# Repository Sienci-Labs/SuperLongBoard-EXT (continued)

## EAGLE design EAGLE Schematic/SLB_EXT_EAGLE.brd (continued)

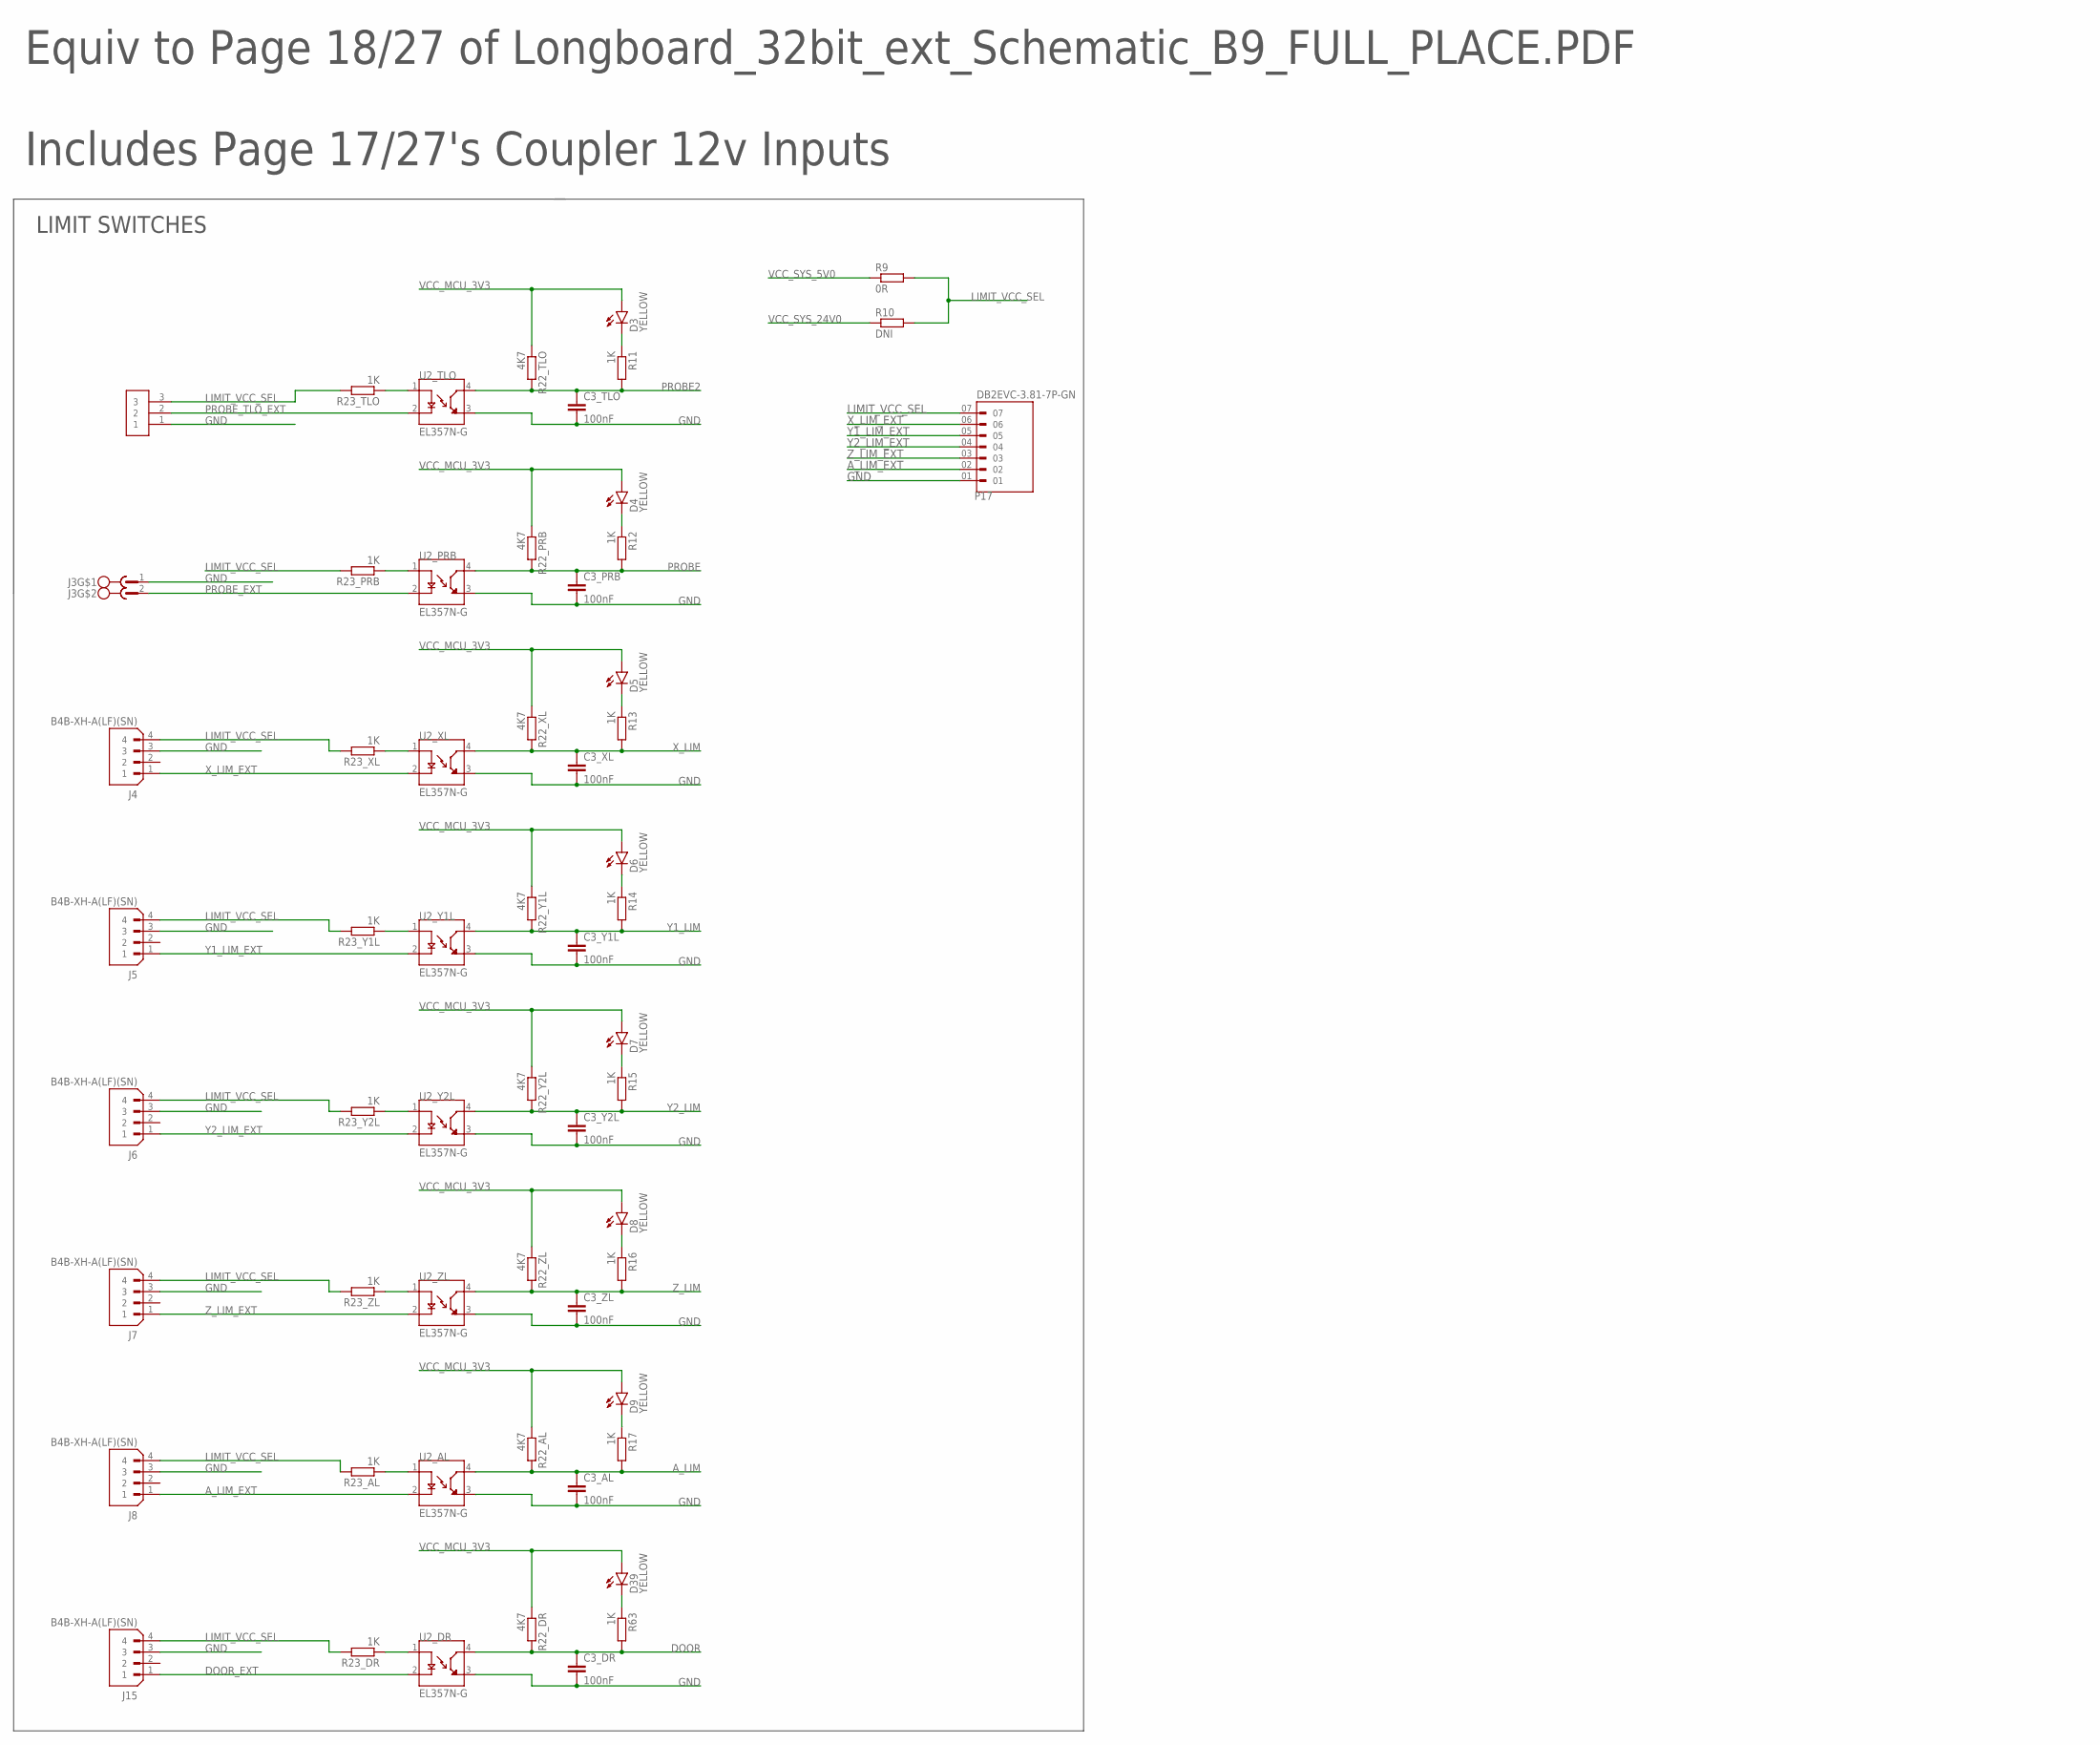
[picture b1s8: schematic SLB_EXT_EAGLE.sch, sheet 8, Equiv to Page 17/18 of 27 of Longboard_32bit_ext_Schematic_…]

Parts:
C3_AL, C3_DR, C3_PRB, C3_TLO, C3_XL, C3_Y1L, C3_Y2L, C3_ZL: 100nF; C0402
D3, D4, D5, D6, D7, D8, D9, D39: YELLOW; CHIP-LED0603
J2: Phoenix Pluggable 3.81mm 3 way; 3.81MM-3WAY-PLUGGABLE-SCREW
J3: Phoenix Pluggable 3.81mm 2 way; MC1.5/2-G-3.81
J4, J5, J6, J7, J8, J15: B4B-XH-A(LF)(SN); JST_B4B-XH-A(LF)(SN)
P17: DB2EVC-3.81-7P-GN; PHOENIX_1803471
R9: 0R; R0603
R10: DNI; R0603
R11, R12, R13, R14, R15, R16, R17, R63: 1K; R0402
R22_AL, R22_DR, R22_PRB, R22_TLO, R22_XL, R22_Y1L, R22_Y2L, R22_ZL: 4K7; R0402
R23_AL, R23_DR, R23_PRB, R23_TLO, R23_XL, R23_Y1L, R23_Y2L, R23_ZL: 1K; R0603
U2_AL, U2_DR, U2_PRB, U2_TLO, U2_XL, U2_Y1L, U2_Y2L, U2_ZL: EL357N-G; OPTO_EL357N-G

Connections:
A_LIM: C3_AL.1, R17.2, R22_AL.2, U2_AL.4 (CT); also elsewhere on the board
A_LIM_EXT: J8.1, P17.02, U2_AL.2 (C)
DOOR: C3_DR.1, R22_DR.2, R63.2, U2_DR.4 (CT); also elsewhere on the board
DOOR_EXT: J15.1, U2_DR.2 (C); also elsewhere on the board
GND: C3_AL.2, C3_DR.2, C3_PRB.2, C3_TLO.2, C3_XL.2, C3_Y1L.2, C3_Y2L.2, C3_ZL.2, J2.1, J3.1, J4.3, J5.3, J6.3, J7.3, J8.3, J15.3, P17.01, U2_AL.3 (ET), U2_DR.3 (ET), U2_PRB.3 (ET), U2_TLO.3 (ET), U2_XL.3 (ET), U2_Y1L.3 (ET), U2_Y2L.3 (ET), U2_ZL.3 (ET); also elsewhere on the board
LIMIT_VCC_SEL: J2.3, J4.4, J5.4, J6.4, J7.4, J8.4, J15.4, P17.07, R9.2, R10.2, R23_AL.2, R23_DR.2, R23_PRB.2, R23_TLO.2, R23_XL.2, R23_Y1L.2, R23_Y2L.2, R23_ZL.2
unnamed: R23_TLO.1, U2_TLO.1 (A)
unnamed: D3.C, R11.1
unnamed: R23_PRB.1, U2_PRB.1 (A)
unnamed: D4.C, R12.1
unnamed: R23_XL.1, U2_XL.1 (A)
unnamed: D5.C, R13.1
unnamed: R23_Y1L.1, U2_Y1L.1 (A)
unnamed: D6.C, R14.1
unnamed: R23_Y2L.1, U2_Y2L.1 (A)
unnamed: D7.C, R15.1
unnamed: R23_ZL.1, U2_ZL.1 (A)
unnamed: D8.C, R16.1
unnamed: R23_AL.1, U2_AL.1 (A)
unnamed: D9.C, R17.1
unnamed: R23_DR.1, U2_DR.1 (A)
unnamed: D39.C, R63.1
PROBE: C3_PRB.1, R12.2, R22_PRB.2, U2_PRB.4 (CT); also elsewhere on the board
PROBE2: C3_TLO.1, R11.2, R22_TLO.2, U2_TLO.4 (CT); also elsewhere on the board
PROBE_EXT: J3.2, U2_PRB.2 (C)
PROBE_TLO_EXT: J2.2, U2_TLO.2 (C)
VCC_MCU_3V3: D3.A, D4.A, D5.A, D6.A, D7.A, D8.A, D9.A, D39.A, R22_AL.1, R22_DR.1, R22_PRB.1, R22_TLO.1, R22_XL.1, R22_Y1L.1, R22_Y2L.1, R22_ZL.1; also elsewhere on the board
VCC_SYS_5V0: R9.1; also elsewhere on the board
VCC_SYS_24V0: R10.1; also elsewhere on the board
X_LIM: C3_XL.1, R13.2, R22_XL.2, U2_XL.4 (CT); also elsewhere on the board
X_LIM_EXT: J4.1, P17.06, U2_XL.2 (C)
Y1_LIM: C3_Y1L.1, R14.2, R22_Y1L.2, U2_Y1L.4 (CT); also elsewhere on the board
Y1_LIM_EXT: J5.1, P17.05, U2_Y1L.2 (C)
Y2_LIM: C3_Y2L.1, R15.2, R22_Y2L.2, U2_Y2L.4 (CT); also elsewhere on the board
Y2_LIM_EXT: J6.1, P17.04, U2_Y2L.2 (C)
Z_LIM: C3_ZL.1, R16.2, R22_ZL.2, U2_ZL.4 (CT); also elsewhere on the board
Z_LIM_EXT: J7.1, P17.03, U2_ZL.2 (C)

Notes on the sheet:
Equiv to Page 18/27 of Longboard_32bit_ext_Schematic_B9_FULL_PLACE.PDF Includes Page 17/27's Coupler 12v Inputs
LIMIT SWITCHES

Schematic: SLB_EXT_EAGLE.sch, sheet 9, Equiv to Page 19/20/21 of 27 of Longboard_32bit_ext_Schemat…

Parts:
C10: 100nF; C0402; LCSC_PART C576517
C11, C12, C14, C15, C58, C59: 10uF; C1206; LCSC_PART C576517
C13, C52, C53: 22uF; C0805; LCSC_PART C576517
C16: 10nF; C0402; LCSC_PART C576517
C17: 10pF; C0603; LCSC_PART C576517
C18, C19, C85: 8.2nF; C0603; LCSC_PART C576517
C54: 4.7uF; C0603
C55: 22uF; C0603; LCSC_PART C576517
C56: 100uF; CAPMP3528X210N
C57: 100uF; SANYO-OSCON_SMD_C6
C69, C76: 100nF 100v; C0805; LCSC_PART C576517
C74: 10uF 100V; C0603; LCSC_PART C576517
C75: 2.2uF; C1206; LCSC_PART C576517
C77, C78, C79, C80, C89, C90: 10uF; C1206
C81: 100nF 100v; C0603; LCSC_PART C576517
C83: 1.5nF; C0603; LCSC_PART C576517
C84: 5.6pF; C0402; LCSC_PART C576517
C86: 220pF; C0603; LCSC_PART C576517
C113: 100nF; C0603; LCSC_PART C576517
C115: 10uF 100V; C1210; LCSC_PART C576517
C144, C145: 10uF 100V; C0805; LCSC_PART C576517
D14: SS210; DO-214AC; LCSC_PART C14996
D19: SS54; DO-214AC; LCSC_PART C14996
D20, D24: GREEN; CHIP-LED0603
D23: 1SMAF4734A; SMAF-ZDIODE
D32: RED; CHIP-LED0805
J19: DNI; 1X02
L3: 22uH; YSPI0630A-220M
L5: 68uH; DR125
L7: 150mΩ ±25% 220Ω@100MHz 0805 Ferrite Beads ROHS; FB402; LCSC_PART C139188
L8, L9, L12: 150mΩ ±25% 220Ω@100MHz 0805 Ferrite Beads ROHS; FB805; LCSC_PART C139188
P10: DB2ERC-5.08-2P-GN; MSTBA2
P23: 22284020; 1X02
P24: 1803329; PHOENIX_1803329
Q3: 2N7002-7-F; SOT-23
Q14, Q15: CSD19538Q3A
R29, R134: 2R2; R0603
R30: 180K; R0603
R38, R55, R82, R83: 10K; R0603
R43: 8K2; R0603
R56: 47k; R0603
R57: 1K91; R0603
R111, R196: 1K; R0603
R125, R132: 20K; R0603
R167: 1k5; R0603
R175: 4K7; R0603
R176: 18K; R0603
R177, R184: 5K1; R0603
R178: 620R; R0603
R179: 39K; R0603
S1: SS-12D11G5R; XKBENTERPRISESS-12D11G5R
U16: TPS54331DR; SOIC127P599X175-8N
U24: LM5146QRGYTQ1; RGY0020B
U43: EL357N-G; OPTO_EL357N-G
VR1: AMS1117-3.3

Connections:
COMP: C85.1, C86.1, U24.4 (COMP)
ESTOP_5V_EN: P23.1, P24.06
FEEDBACK24V: C83.2, C86.2, R176.1, R177.1, R178.2, U24.5 (FB)
GND: C11.2, C12.2, C13.2, C14.2, C15.2, C16.2, C17.1, C18.2, C19.1, C52.2, C53.2, C54.2, C58.2, C59.2, C69.2, C74.2, C75.2, C76.2, C77.2, C78.2, C79.2, C80.2, C84.2, C89.2, C90.2, C113.2, C115.2, C144.2, C145.2, D19.2 (A), J19.2, L9.1, P10.2, P24.01, Q15.1 (SOURCE), Q15.2 (SOURCE), Q15.3 (SOURCE), R43.2, R57.2, R82.2, R83.2, R178.1, R179.2, S1.LEFT, U16.7 (GND), U24.6 (AGND), U24.9 (NC_2), U24.12 (PGND), U24.15 (EP_2), U24.16 (NC), U24.21 (EP), U43.2 (C), VR1.1 (ADJ/GND); also elsewhere on the board
HALT_EXT: D32.C, Q3.P3 (D), R38.2; also elsewhere on the board
INPUT_VCC: C89.1, C90.1, L7.1, P10.1; also elsewhere on the board
MACRO1_EXT: P24.04; also elsewhere on the board
MACRO2_EXT: P24.03; also elsewhere on the board
MCU_GND: C55.2, C56.2, C57.-, D23.A, L9.2, Q3.P2 (S); also elsewhere on the board
MOTOR_NPGD: Q3.P1 (G); also elsewhere on the board
MOTOR_VCC_80V: R184.2; also elsewhere on the board
unnamed: D14.2 (A), L7.2
unnamed: C10.2, D19.1 (C), L3.1, U16.8 (PH)
unnamed: R29.2, U24.20 (VIN)
unnamed: C76.1, U24.3 (SS_TRK)
unnamed: R125.2, U24.8 (SYNCIN)
unnamed: R132.2, U24.10 (PGOOD)
unnamed: C75.1, R125.1, R132.1, U24.14 (VCC)
unnamed: Q14.4 (GATE), U24.18 (HO)
unnamed: C85.2, R177.2
unnamed: Q15.4 (GATE), U24.13 (LO)
unnamed: C84.1, R167.1, U24.11 (ILIM)
unnamed: R134.1, U24.17 (BST)
unnamed: C81.1, R134.2
unnamed: C81.2, L5.1, Q14.1 (SOURCE), Q14.2 (SOURCE), Q14.3 (SOURCE), Q15.5 (DRAIN), Q15.6 (DRAIN), Q15.7 (DRAIN), Q15.8 (DRAIN), Q15.9 (DRAIN), Q15.10 (DRAIN), Q15.11 (DRAIN), Q15.12 (DRAIN), R167.2, U24.19 (SW)
unnamed: C83.1, R175.1
unnamed: C18.1, U16.4 (SS)
unnamed: C10.1, U16.1 (BOOT)
unnamed: C19.2, R56.2
unnamed: D24.C, R83.1
unnamed: C17.2, R56.1, U16.6 (COMP)
unnamed: D20.C, R82.1
unnamed: L12.1, P24.07
unnamed: D32.A, R111.2
unnamed: R184.1, U43.1 (A)
unnamed: R196.2, U43.4 (CT)
POWER_IND: P24.05, U43.3 (ET)
PWR_EN: C113.1, R30.2, R43.1, S1.CENTER, U24.1 (EN_UVLO)
PWR_IN_36-80V: C69.1, C74.1, C115.1, C144.1, C145.1, D14.1 (C), Q14.5 (DRAIN), Q14.6 (DRAIN), Q14.7 (DRAIN), Q14.8 (DRAIN), Q14.9 (DRAIN), Q14.10 (DRAIN), Q14.11 (DRAIN), Q14.12 (DRAIN), R29.1, R30.1
RT: R179.1, U24.2 (RT)
START_EXT: P24.02; also elsewhere on the board
VCC_MCU_3V3: C59.1, D24.A, VR1.2 (OUT), VR1.4 (OUT); also elsewhere on the board
VCC_MCU_5V0: C54.1, C55.1, C56.1, C57.+, C58.1, D23.C, L8.1, L8.2, VR1.3 (IN); also elsewhere on the board
VCC_SYS_5V0: C11.1, C12.1, C13.1, C14.1, C52.1, C53.1, D20.A, J19.1, L3.2, L12.2, P23.2, R38.1, R55.1, R111.1; also elsewhere on the board
VCC_SYS_24V0: C15.1, C16.1, C77.1, C78.1, C79.1, C80.1, L5.2, R175.2, R176.2, R196.1, U16.2 (VIN); also elsewhere on the board
VSENSE: R55.2, R57.1, U16.5 (VSENSE)

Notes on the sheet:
Equiv to Page 19/27 of Longboard_32bit_ext_Schematic_B9_FULL_PLACE.PDF Includes Page20 of 27's 5v Power Supply Includes Page21 of 27's 24v Power Supply
DC POWER REGULATION
5V POWER SUPPLY
24V POWER SUPPLY
24.03v Output
Pin3 should be floating if unused.
POWER SWITCH
This switch will turn off all power by disabling 24V supply.
POWER LEDS
POWER HALT
POWER FILTERING AND MCU RAIL
3.3V REGULATOR
MUSHROOM BYPASS
EMERGENCY STOP

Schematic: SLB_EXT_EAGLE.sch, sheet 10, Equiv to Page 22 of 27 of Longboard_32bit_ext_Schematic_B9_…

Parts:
C87, C88: 10uF; C1206; LCSC_PART C576517
C91: 10uF 100V; C1210; LCSC_PART C576517
C92: 4.7uF; C0603; LCSC_PART C576517
C93, C104, C105, C108, C140, C142: 100nF; C0603; LCSC_PART C576517
C94: 10uF; C0603; LCSC_PART C576517
C99: 4.7uF; C0805; LCSC_PART C576517
C103: 10uF; C0805; LCSC_PART C576517
C106: 470nF; C0603; LCSC_PART C576517
C139: 4.7uF; C1206; LCSC_PART C576517
C141: 1uF; C0603; LCSC_PART C576517
C143: 22uF; C1206; LCSC_PART C576517
D36: MM3Z10VST1G; SOD-323F
D45, D47, D48: SS210; DO-214AC; LCSC_PART C14996
D46, D50: SMBJ85CA; SMBJ
D49: ZMM5V6-M; MINIMELF
D56: B5819W; SOD123FL
D57: BLUE; CHIP-LED0603
D58: RED; CHIP-LED0603
F3: 24V 460mA; 1206L
K2: VCF4-1000; TE_VCF4-1000
P6: WJ15EDGK-3.81-2P; DB2EVC-3.81-2P-GN
Q1: WSF50P10; TO252
Q13: ST3422A; SOT-23
Q16, Q17: BSS123; SOT95P240X110-3N
R42, R209, R210, R211: 0R; R0603
R70: 100R; R0603
R103, R198: 4K7; R0603
R104, R159: B57235S0100M000; B57164
R106, R162: 3K3; R0603
R126: 0.003R; R1206
R127, R212, R215: DNI; R0603
R128: 4.7R; R0603
R129: 100R; R1206
R130, R181, R197, R202: 10K; R0603
R133: 24K; R0603
R163: 100k; R0603
R173: 510K; R0603
R180, R213: 2K2; R0603
R182: DNI; R1206
R183: 100K; R0603
R199: 470K; R0603
R200, R203, R204: 1K; R0603
R201: 330K; R0603
U25: 74LVC1G08GW-Q100,1; SOT65P210X110-5N
U40: LM393DR2G; SOIC127P600X265-8N
U41: INA280A3IDCKR; DCK0005A-IPC_A
U42: SN74HC00DR; SOIC127P600X175-14N
U44: SN74LVC1G32DCKR; SOT65P210X110-5N
U50: NE555DR; SOIC-8

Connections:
5V_VCC: C104.1, C105.2, C108.2, C140.1, R106.2, R130.1, R162.2, R200.1, R201.1, U25.5 (VCC), U40.8 (VCC), U42.14 (VCC), U44.5 (VCC), U50.4 (RST), U50.8 (VCC)
24V_RELAY: D45.2 (A), F3.1, K2.86, P6.1
CTRL: C142.1, U50.5 (CTRL)
CURRENT_SENSE: C94.1, R70.2, R173.2, R210.1, R212.1
ESTOP_EN: C99.1, C103.1, D49.C, R180.1, U42.1 (1A), U42.12 (4A)
FAULT1+: R163.2, R211.2, R212.2, U40.3 (IN_A)
FAULT1-: R210.2, R215.2, U40.2 (IN_A_2)
FAULT2: R162.1, R183.1, U40.7 (OUT_B)
GND: C87.2, C88.2, C92.2, C93.2, C94.2, C99.2, C103.2, C104.2, C105.1, C106.2, C108.1, C139.2, C140.2, C142.2, C143.2, D46.A, D48.2 (A), D49.A, D50.A, Q13.P2 (S), Q17.S, R127.2, R133.2, R173.1, R180.2, R181.1, R182.1, R202.2, R203.2, R204.2, R209.2, U25.3 (GND), U40.4 (GND), U41.2 (GND), U42.7 (GND), U44.3 (GND), U50.1 (GND); also elsewhere on the board
INPUT_INRUSH: Q1.3 (D), R104.2, R126.1, U41.4 (IN+)
INPUT_VCC: C87.1, C88.1, D36.C, D50.C, Q1.2 (S), R127.1, R159.1, R197.1; also elsewhere on the board
MOTOR_NPGD: U44.4 (Y); also elsewhere on the board
MOTOR_VCC_80V: C91.2, D46.C, D48.1 (C), K2.87; also elsewhere on the board
unnamed: R104.1, R159.2
unnamed: D47.2 (A), K2.30, R126.2, R129.1, U41.5 (IN-)
unnamed: C91.1, D47.1 (C), R129.2
unnamed: Q13.P1 (G), R128.2
unnamed: F3.2, Q13.P3 (D)
unnamed: R70.1, U41.1 (OUT)
unnamed: D57.A, R213.1, U25.4 (Y)
unnamed: D57.C, R203.1
unnamed: C139.1, D56.A, R199.1, U25.2 (A)
unnamed: Q16.D, R103.2
unnamed: Q16.S, R209.1
unnamed: Q16.G, R213.2
unnamed: R181.2, U40.6 (IN_B_2)
unnamed: R183.2, U40.5 (IN_B)
unnamed: D58.C, R204.1
unnamed: R42.2, R106.1, R163.1, U40.1 (OUT_A)
unnamed: U42.2 (1B), U42.10 (3B), U42.11 (4Y)
unnamed: U42.8 (3Y), U42.13 (4B)
NTC_BYP_GATE: D36.A, Q1.1 (G), R103.1, R197.2
OCP1_THRS: R130.2, R133.1, R211.1, R215.1
OVERCURRENT_L: C106.1, R42.1, U42.9 (3A)
RELAY_ACT: C141.1, D56.C, R198.2, R199.2, U25.1 (B), U42.6 (2Y)
RELAY_GATE: Q17.D, R128.1, R182.2, R198.1
RELAY_GATE_N: U42.3 (1Y), U42.4 (2A), U42.5 (2B), U44.2 (B)
TIMER_OUT: D58.A, Q17.G, R202.1, U44.1 (A), U50.3 (OUT)
TRIG: C141.2, C143.1, R200.2, R201.2, U50.2 (TRIG), U50.7 (DIS)
VCC_SYS_5V0: C92.1, C93.1, U41.3 (VS); also elsewhere on the board
VCC_SYS_24V0: D45.1 (C), K2.85, P6.2; also elsewhere on the board

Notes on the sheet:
Equiv to Page 22/27 of Longboard_32bit_ext_Schematic_B9_FULL_PLACE.PDF
INRUSH CURRENT LIMITING
CURRENT SENSE
MAIN RELAY
CONTACTOR
Estop enable is connected from system 5V and is filtered here.
3.51V at 11.7A
Rework here for first 50 boards is to drop a 16.7K resistor onto R130, but BOM change is on R133 to 24K.
Enable Lockout should have a time constant of 10s
NTC BYPASS BUFFER
OVERCURRENT COMPARATOR
LOCKOUT TIMER
ESTOP FILTER
QUAD-NAND forms latching fault switch, reset by re-enabling etsop
LOCKOUT LATCH
LOCKOUT HALT

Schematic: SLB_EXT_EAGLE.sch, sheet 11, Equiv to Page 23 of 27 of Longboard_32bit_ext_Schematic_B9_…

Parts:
C4, C73: 100nF; C0603; LCSC_PART C576517
D2: WHITE; CHIP-LED0603
D28: RED; CHIP-LED0603
J9: 1803455; PHOENIX_1803455
J11: 1803280; PHOENIX_1803280
Q4, Q5, Q11, Q12: 2N7002-7-F; SOT-23
R24, R25, R31, R32, R35, R36, R37, R40, R41: 220R; R0402
R26, R84, R153, R154, R166, R168, R169: 10K; R0402
R34: 300R; R0402
R99: DNI; R0402
R151, R152: 4K7; R0402
R164: 4k7; R0402
R165: 510R; R0402
U3: SN74LVC2G17DBVR; SOT95P280X145-6N
U4, U5, U6, U7, U8, U10, U23: EL357N-G; OPTO_EL357N-G

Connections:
GND: C4.2, J9.05, J11.01, R26.2, U3.2 (GND), U5.3 (ET), U6.3 (ET), U23.2 (C); also elsewhere on the board
LASER_EN: Q12.P1 (G), R37.2, R166.1; also elsewhere on the board
LASER_EN_EXT: J11.03, R168.1, U8.3 (ET)
LASER_PWM: Q5.P1 (G), R41.2, R154.2; also elsewhere on the board
LASER_PWM_EXT: J11.02, U3.6 (1Y)
LASER_PWM_ISO: R169.1, U3.1 (1A), U10.3 (ET)
MCU_GND: C73.2, Q4.P2 (S), Q5.P2 (S), Q11.P2 (S), Q12.P2 (S), R84.2, R99.2, R153.1, R154.1, R166.2, R168.2, R169.2, U4.2 (C), U5.2 (C), U8.2 (C), U23.3 (ET); also elsewhere on the board
unnamed: R25.1, U4.1 (A)
unnamed: R24.2, U4.4 (CT)
unnamed: R31.1, U5.1 (A)
unnamed: R165.1, U23.1 (A)
unnamed: R32.1, U6.1 (A)
unnamed: R34.2, U7.4 (CT)
unnamed: D2.A, R151.1
unnamed: R35.1, U7.1 (A)
unnamed: D2.C, Q4.P3 (D)
unnamed: D28.A, R152.1
unnamed: D28.C, Q5.P3 (D)
unnamed: R41.1, U10.1 (A)
unnamed: Q12.P3 (D), R99.1, U10.2 (C)
unnamed: R37.1, U8.1 (A)
unnamed: R36.2, U8.4 (CT)
unnamed: R40.2, U10.4 (CT)
SPINDLE_CONN: J9.04, U3.4 (2Y)
SPINDLE_DIR: R31.2; also elsewhere on the board
SPINDLE_EN: Q11.P1 (G), R84.1; also elsewhere on the board
SPINDLE_EN_5V: U7.3 (ET); also elsewhere on the board
SPINDLE_PWM: Q4.P1 (G), R25.2, R153.2; also elsewhere on the board
SPINDLE_PWM_ISO: R26.1, U3.3 (2A), U4.3 (ET)
SPIN_AT_SPEED: J9.01, R165.2
SPIN_DIR_12V: J9.03, U5.4 (CT)
SPIN_EN: Q11.P3 (D), U6.2 (C), U7.2 (C)
SPIN_EN_12V: J9.02, U6.4 (CT)
SPIN_SPEED: C73.1, R164.1, U23.4 (CT); also elsewhere on the board
VCC_MCU_3V3: R32.2, R35.2, R164.2; also elsewhere on the board
VCC_MCU_5V0: R34.1, R151.2, R152.2; also elsewhere on the board
VCC_SYS_5V0: C4.1, R24.1, R36.1, R40.1, U3.5 (VCC); also elsewhere on the board

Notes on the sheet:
Equiv to Page 23/27 of Longboard_32bit_ext_Schematic_B9_FULL_PLACE.PDF
Spindle
Laser
U3_1
ON EXPANSION HEADER

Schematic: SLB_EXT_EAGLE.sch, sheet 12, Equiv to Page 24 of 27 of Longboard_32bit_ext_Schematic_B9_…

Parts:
C60: 4.7uF; C0603
C61: 22uF; C0603; LCSC_PART C576517
C62, C63, C65, C66: 100nF; C0603; LCSC_PART C576517
C64: 1uF; C0603; LCSC_PART C576517
D25: RED; CHIP-LED0603
D26: GREEN; CHIP-LED0603
D41: ZMM5V6-M; LL-34
D42: ZMM3V3-M; LL-34
J14: KH-PCB-6P6C
L10, L11: 150mΩ ±25% 220Ω@100MHz 0805 Ferrite Beads ROHS; FB805; LCSC_PART C139188
R85, R88: 200R; R0402
R86: 47K; R0402
R87: 120R; R0402
R90, R91, R92, R93, R94, R95: 2K; R0402
U18: CBMUD1201LAS8; SOIC-8
U19: PCA82C250T/YM; SO8
U21, U22: EL357N-G; OPTO_EL357N-G

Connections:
CANH: J14.2, R87.2, U19.7 (CANH)
CANL: J14.3, R87.1, U19.6 (CANL)
CAN_RX: R94.1, U18.2 (VOA); also elsewhere on the board
CAN_TX: R95.1, U18.3 (VIB); also elsewhere on the board
GND: C60.2, L11.1; also elsewhere on the board
HALT_PEN: J14.4, U21.2 (C)
HALT_PENDANT: C65.1, R90.1, U21.4 (CT); also elsewhere on the board
KPSTR: C66.1, R92.1, U22.4 (CT); also elsewhere on the board
KPSTR_PEN: J14.5, U22.2 (C)
MCU_GND: C62.2, C65.2, C66.2, D42.A (+), U18.4 (GND1), U21.3 (ET), U22.3 (ET); also elsewhere on the board
unnamed: D25.C, R94.2
unnamed: D26.C, R95.2
unnamed: C62.1, R85.1, U18.1 (VDD1)
unnamed: U18.7 (VIA), U19.4 (RXD)
unnamed: U18.6 (VOB), U19.1 (TXD)
unnamed: C63.2, R88.1, U18.8 (VDD2)
unnamed: R86.2, U19.8 (RS)
unnamed: R91.1, U21.1 (A)
unnamed: R93.1, U22.1 (A)
PENDANT_VCC_5V0: C61.1, C64.1, D41.C (-), J14.1, L10.2, R88.2, R91.2, R93.2, U19.3 (VCC)
PEND_GND: C61.2, C63.1, C64.2, D41.A (+), J14.6, L11.2, R86.1, U18.5 (GND2), U19.2 (GND); also elsewhere on the board
VCC_MCU_3V3: D25.A, D26.A, D42.C (-), R85.2, R90.2, R92.2; also elsewhere on the board
VCC_MCU_5V0: C60.1, L10.1; also elsewhere on the board

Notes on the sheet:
Equiv to Page 24/27 of Longboard_32bit_ext_Schematic_B9_FULL_PLACE.PDF
CANBUS PENDANT
KPSTR = KEYPAD STROBE In grblHAL its now called I2C Strobe: Works with https://github.com/grblHAL/Plugin_keypad

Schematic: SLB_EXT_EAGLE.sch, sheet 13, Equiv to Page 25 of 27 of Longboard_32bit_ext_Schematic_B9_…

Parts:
D27: USBLC6-2SC6; SOT95P280X145-6N
J20: USB-C-Socket; USB-C-16P
L13: DLW21HN900SQ2L; FIL_DLW21HN900SQ2L
R107, R108: 4K7; R0402

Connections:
CONN_USB_D_N: D27.3 (I/O2_IN), D27.4 (I/O2_OUT), J20.A7 (D-), J20.B7 (D-), L13.1
CONN_USB_D_P: D27.1 (I/O1_IN), D27.6 (I/O1_OUT), J20.A6 (D+), J20.B6 (D+), L13.4
MCU_GND: D27.2 (GND), J20.GND, J20.GND2 (GND), J20.SHLD1 (SHLD), J20.SHLD2 (SHLD), J20.SHLD3 (SHLD), J20.SHLD4 (SHLD), J20.SHLD5 (SHLD), J20.SHLD6 (SHLD), J20.SHLD7 (SHLD), J20.SHLD8 (SHLD), R107.1, R108.1; also elsewhere on the board
USBC_CC1: J20.A5 (CC1), R108.2
USBC_CC2: J20.B5 (CC2), R107.2
USB_D_N: L13.2; also elsewhere on the board
USB_D_P: L13.3; also elsewhere on the board
VBUS: D27.5 (VBUS), J20.VBUS1 (VBUS), J20.VBUS2 (VBUS)

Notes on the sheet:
Equiv to Page 25/27 of Longboard_32bit_ext_Schematic_B9_FULL_PLACE.PDF
USB

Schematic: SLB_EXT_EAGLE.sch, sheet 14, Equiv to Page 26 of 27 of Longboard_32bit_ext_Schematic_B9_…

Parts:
C7: 4.7uF; C0603
C8: 22uF; C0603; LCSC_PART C576517
C9: 1uF; C0603; LCSC_PART C576517
C134, C135: 100nF; C0603; LCSC_PART C576517
D1: ZMM3V3-M; LL-34
D16: SM712; SOT23
D17: RED; CHIP-LED0603
D18: GREEN; CHIP-LED0603
D40: ZMM5V6-M; LL-34
J10: DB2EVC-3.81-4P-GN
J12: KH-PCB-6P6C
L1, L2: 150mΩ ±25% 220Ω@100MHz 0805 Ferrite Beads ROHS; FB805; LCSC_PART C139188
R44, R45, R50: 200R; R0402
R46, R48: 560R; R0402
R47, R52, R53, R54: 2K; R0402
R49: 130R; R0402
R51: 220R; R0402
U12: CBMUD1201LAS8; SOIC-8
U13: SN75176BDR; SOIC127P599X175-8N
U15: EL357N-G; OPTO_EL357N-G

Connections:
A: D16.2 (Z2), J10.03, J12.4, R48.1, R49.2, U13.6 (A)
B: D16.1 (Z1), J10.04, J12.3, R46.2, R49.1, U13.7 (B)
DI: R50.2, U12.6 (VOB)
GND: C7.2, L2.1; also elsewhere on the board
MCU_GND: C134.2, D1.A (+), U12.4 (GND1), U15.2 (C); also elsewhere on the board
MOD_GND: C8.2, C9.1, D16.3 (COM), D40.A (+), J10.01, J12.1, J12.6, L2.2, R46.1, R52.2, U12.5 (GND2), U13.5 (GND)
unnamed: C134.1, R44.1, U12.1 (VDD1)
unnamed: C135.2, R45.1, U12.8 (VDD2)
unnamed: R50.1, U13.4 (D)
unnamed: R51.1, U15.1 (A)
unnamed: D17.C, R53.2
unnamed: D18.C, R54.2
PEND_GND: C135.1; also elsewhere on the board
RE: R52.1, U13.2 (!RE), U13.3 (DE), U15.3 (ET)
RO: R47.1, U12.7 (VIA), U13.1 (R)
RS485_DIR: R51.2; also elsewhere on the board
RXD_RS485: R53.1, U12.2 (VOA); also elsewhere on the board
TXD_RS485: R54.1, U12.3 (VIB); also elsewhere on the board
VCC_MCU_3V3: D1.C (-), D17.A, D18.A, R44.2; also elsewhere on the board
VCC_SYS_5V0: C7.1, L1.1; also elsewhere on the board
VCC_SYS_5V0_RS485: C8.1, C9.2, D40.C (-), J10.02, L1.2, R45.2, R47.2, R48.2, U13.8 (VCC), U15.4 (CT)

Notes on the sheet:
Equiv to Page 26/27 of Longboard_32bit_ext_Schematic_B9_FULL_PLACE.PDF
RS-485

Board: 2 copper layers, 706 parts (0 on the bottom side), 421 nets, no tracks yet.

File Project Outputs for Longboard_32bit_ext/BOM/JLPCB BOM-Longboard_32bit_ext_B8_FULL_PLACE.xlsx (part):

Quantity | Manufacturer Part Number | Manufacturer | Description | SuppliersPartNumber | Designator | Comment
30 | CC0603KRX7R9BB104 | YAGEO | 50V 100nF X7R ±10% 0603 Multilayer Ceramic Capacitors MLCC - SMD/SMT ROHS, Chip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 | C14663 | C1, C2, C4, C6, C10, C41, C42, C43, C44, C45, C47, C48, C49, C50, C65, C66, C67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 | 100nF
48 | CL05B104KO5NNNC | Samsung Electro-Mechanics | 16V 100nF X7R ±10% 0402 Multilayer Ceramic Capacitors MLCC - SMD/SMT ROHS | C1525 | C3_AL, C3_CY, C3_DR, C3_HL, C3_MC1, C3_MC2, C3_PRB, C3_TLO, C3_XL, C3_Y1L, C3_Y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 | 100nF
10 | CL10A105KB8NNNC | Samsung Electro-Mechanics | Chip capacitors | C15849 | C5, C9, C27, C28, C40, C46, C64, C94, C98, C141 | 1uF
2 | CL21A475KAQNNNE | Samsung Electro-Mechanics | Chip capacitors | C1779 | C7, C60 | 4.7uF
8 | CL21A226MAQNNNE | Samsung Electro-Mechanics | 25V 22uF X5R ±20% 0805 Multilayer Ceramic Capacitors MLCC - SMD/SMT ROHS | C45783 | C8, C13, C52, C53, C55, C61, C123, C131 | 22uF
15 | CL31A106KBHNNNE, 1206B475K500NT | Samsung Electro-Mechanics, Guangdong Fenghua Advanced Tech | 50V 10uF X5R ±10% 1206 Multilayer Ceramic Capacitors MLCC - SMD/SMT ROHS, Chip 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 | C13585 | C11, C12, C14, C15, C58, C59, C77, C78, C79, C80, C87, C88, C89, C90, C143 | 10uF
1 | 0603B103K500NT | Guangdong Fenghua Advanced Tech | 50V 10nF X7R ±10% 0603 Multilayer Ceramic Capacitors MLCC - SMD/SMT ROHS | C57112 | C16 | 10nF
3 | CL10C100JB8NNNC | Samsung Electro-Mechanics | Chip capacitors | C1634 | C17, C38, C39 | 10pF
4 | CC0603KRX7R9BB822 | YAGEO | 50V 8.2nF X7R ±10% 0603 Multilayer Ceramic Capacitors MLCC - SMD/SMT ROHS | C113812 | C18, C19, C20, C85 | 8.2nF
9 | CL10A475KO8NNNC | Samsung Electro-Mechanics | 16V 4.7uF X5R ±10% 0603 Multilayer Ceramic Capacitors MLCC - SMD/SMT ROHS | C19666 | C23, C25, C26, C54, C92, C99, C100, C124, C132 | 4.7uF
1 | TAJB107K006RNJ | AVX | Tantalum capacitor | C16133 | C56 | 100uF
1 | HV101M035E077ETR | Capxon International Elec | -45℃~+105℃ 2000hrs@105℃ 100uF 7.7mm 35V 6.3mm ±20% SMD,6.3x7.7mm Aluminum Elect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 | C59934 | C57 | 100uF
3 | 0805B104K101NT | Guangdong Fenghua Advanced Tech | Chip capacitors | C89258 | C69, C76, C81 | 100nF 100V
5 | GRM32EC72A106KE05L | Murata | Chip capacitors | C576517 | C74, C91, C115, C144, C145 | 10uF 100V
1 | CL31A225KBHNNNE | Samsung Electro-Mechanics | Chip capacitors | C170101 | C75 | 2.2uF 100V
2 | CL05A105KA5NQNC | Samsung Electro-Mechanics | Chip capacitor | C52923 | C82, C101 | 1.0uF
1 | 0603B152K500NT | Guangdong Fenghua Advanced Tech | Chip capacitors | C1595 | C83 | 1.5nF
1 | GQM1875C2E5R6BB12D | Murata | Chip capacitors | C2297617 | C84 | 5.6pF
1 | CL10B221KB8NNNC | Samsung Electro-Mechanics | Chip capacitors | C1603 | C86 | 220pF
3 | CL05B103KB5NNNC | Samsung Electro-Mechanics | Chip capacitors | C15195 | C97, C109, C118 | 10nF
1 | CL10A106KP8NNNC | Samsung Electro-Mechanics | Chip capacitors | C19702 | C103 | 10uF
1 | CL10B474KA8NNNC | Samsung Electro-Mechanics | Chip capacitors | C1623 | C106 | 470nF
2 | 0402B682K500NT | Guangdong Fenghua Advanced Tech | Chip capacitors | C1542 | C110, C111 | 6.8nF
1 | 0402B223K500NT | Guangdong Fenghua Advanced Tech | Chip capacitors | C1532 | C112 | 22nF
1 | CL31B102KGFNNNE | Samsung Electro-Mechanics | Chip capacitors | C35216 | C114 | 1nF
1 | CL05A475MP5NRNC | Samsung Electro-Mechanics | Chip capacitor | C23733 | C117 | 4.7uF
2 | GRM1555C1H100JA01D | Murata Electronics | Chip capacitors | C76946 | C120, C121 | 10pF
1 | 1206B475K500NT | Guangdong Fenghua Advanced Tech | Chip capacitors | C29823 | C139 | 4.7uF
2 | ZMM3V3-M | ST(Semtech) | Single 3.1V~3.5V 500mW 3.3V LL-34 Zener Diodes ROHS | C8056 | D1, D42 | ZMM3V3-M
1 | 19-218/T1D-CQ2R2TY/3T | Everlight Elec | White LED | C1322288 | D2 | 0603 White
11 | 19-213/Y2C-CQ2R2L/3T(CY) | Everlight Elec | -40℃~+85℃ 585.5nm~591.5nm Yellow 120° 60mW 0603 Light Emitting Diodes (LED) ROHS | C72038 | D3, D4, D5, D6, D7, D8, D9, D10, D11, D12, D39 | 0603 Yellow
10 | KT-0603R | Hubei KENTO Elec | -40℃~+85℃ Red 0603 Light Emitting Diodes (LED) ROHS | C2286 | D13, D17, D25, D28, D38, D58, D61, D62, D63, D64 | 0603 Red
4 | SS210 | MDD(Microdiode Electronics) | 100V 2A 850mV @ 2A SMA(DO-214AC) Schottky Barrier Diodes (SBD) ROHS | C14996 | D14, D45, D47, D48 | SS210
14 | MHT192UGCT | MEIHUA | 20mA -40℃~+85℃ 515nm~530nm Emerald 120° 60mW 0603 Light Emitting Diodes (LED) R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 | C389519 | D15_TR1, D15_TR2, D18, D20, D24, D26, D29, D37, D43_RL1, D43_RL2, D51, D52, D59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 | 0603 LED Green
1 | SM712 | DOWO | Bidirectional 12V (Max), 7V (Max) 7.5V / 13.3V 10V / 20V 12A(8/20us) SOT-23-3 T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 | C293966 | D16 | SM712
1 | SS54 | MDD | 40V 5A 550mV@5A | C22452 | D19 | SS54
5 | ZMM5V6 | HXY MOSFET | Single 500mW 5.2V~6V 5.6V LL-34 Zener Diodes ROHS | C5345993 | D21, D22, D40, D41, D49 | ZMM5V6-M
1 | 1SMAF4734A | Shandong Jingdao Microelectronics | 27V ±5% 1W 500nA @ 20.5V SMA(DO-214AC) Zener Diodes RoHS | C169539 | D23 | 1SMAF4734A
1 | USBLC6-2SC6 | TECH PUBLIC | Very low capacitance ESD protection, 3.5 pF, -40 to 125 degC, 6-Pin SOT23, RoHS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 | C2827654 | D27 | USBLC6-2SC6
5 | B5819W SL | Jiangsu Changjing Electronics Technology Co., Ltd. | 40V 600mV@1A 1A SOD-123 Schottky Barrier Diodes (SBD) ROHS | C8598 | D30_RL1, D30_RL2, D31_TR1, D31_TR2, D56 | B5819W SL
1 | NCD0805R1 | Foshan NationStar Optoelectronics | Red 0805 Light Emitting Diodes (LED) ROHS | C84256 | D32 | 0805 LED Red
3 | F.0603.00026/P2-0603B1TS2-06T-001 | TUOZHAN | 5mA -40℃~+85℃ Blue 120° 0603 Light Emitting Diodes (LED) ROHS | C7496819 | D33, D34, D57 | 0603 LED Blue
4 | BAT54S | JSMSEMI | 30V Dual 200mA 800mV@100mA SOT-23 Schottky Barrier Diodes (SBD) ROHS | C916425 | D35, D53, D54, D55 | BAT54S Schottky
1 | MM3Z10VST1G | On Semiconductor | MM3Z10VST1G Zener Diode, 10V 2% 300 mW SMT 2-Pin SOD-323 | ON Semiconductor MM3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 | C235983 | D36 | MM3Z10VST1G
2 | SMBJ85CA | BORN | 4.4A 137V 94.4V 85V DO-214AA Electrostatic and Surge Protection (TVS/ESD) ROHS | C2842381 | D46, D50 | 85V TVS
3 |  | Jinrui Electronic Materials Co. | 24V 200mA 100A 460mA - Resettable Fuses ROHS | C5307785 | F1_RL1, F1_RL2, F3 | 24V 460mA
2 |  | Jinrui Electronic Materials Co. | 24V 1A 0.1s 1206 PTC Resettable Fuses RoHS | C369160 | F2_TR1, F2_TR2 | 24V 1A
1 | PZ254-2-08-S | HCTL | 250V 3A Brick nogging Square Pins 2.5mm 260℃@5S 6mm 16P -40℃~+105℃ 2.54mm Black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 | C3294466 | J1 | PZ254-2-08-S
2 | WJ15EDGRC-3.81-3P | Ningbo Kangnex | 3.81mm Green Board Edge/Receptacle-Close Push-Pull,P=3.81mm Pluggable System Te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 | C8406 | J2, J11 | WJ15EDGRC-3.81-3P
1 | WJ15EDGRC-3.81-2P | Ningbo Kangnex | 3.81mm Green Board Edge/Receptacle-Close Push-Pull,P=3.81mm Pluggable System Te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 | C8387 | J3 | WJ15EDGRC-3.81-2P
6 | XH-4A | BOOMELE(Boom Precision Elec) | 1x4P 4P XH 1 2.5mm 4 Phosphor bronze Plugin,P=2.5mm Wire To Board / Wire To Wir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 | C37815 | J4, J5, J6, J7, J8, J15 | XH-4A
1 | DB2EVC-3.81-5P-GN | DIBO | 3.81mm Green Board Edge/Receptacle-Close Push-Pull,P=3.81mm Pluggable System Te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 | C395701 | J9 | DB2EVC-3.81-5P-GN
1 | DB2EVC-3.81-4P-GN | DIBO | 3.81mm Green Board Edge/Receptacle-Close Push-Pull,P=3.81mm Pluggable System Te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 | C395697 | J10 | DB2EVC-3.81-4P-GN
2 | KH-PCB-6P6C | Shenzhen Kinghelm Elec | RJ45 RJReceptacle No 1 Shrouded Without LED -45℃~+85℃ Plugin Ethernet Connector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 | C2683354 | J12, J14 | KH-PCB-6P6C
13 | DB2EVC-3.81-2P-GN | DIBO | 3.81mm Green Board Edge/Receptacle-Close Push-Pull,P=3.81mm Pluggable System Te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 | C395686 | J13, J17, P1, P2, P3, P4, P6, P18_RL1, P18_RL2, P19, P21_TR1, P21_TR2, P28 | DB2EVC-3.81-2P-GN
7 | WJ15EDGK-3.81-2P | Ningbo | 2 1 3.81mm Green Plug P=3.81mm Pluggable System Terminal Block ROHS | C8466 | J16, J31_RL1, J31_RL2, J32, J33_TR1, J33_TR2, J34 | WJ15EDGK-3.81-2P
2 | B3B-XH-A(LF)(SN) | JST Sales America | Connector Header Through Hole 3 position 0.098" (2.50mm) | C144394 | J18, J21 | B3B-XH-A(LF)(SN)
1 | TYPE-C-31-M-12 | HRO Electronics Co., Ltd. | USB Connectors 24 Receptacle 1 8.94*7.3mm RoHS | C2765186 | J20 | TYPE-C-31-M-12
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
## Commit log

2024-02-14 Initial commit of original SLB files to be modified.
2024-02-16 Commit some updates around the MOSFET selection and overall DC power section.
2024-02-20 Commit current WIP power supply.
2024-02-20 Commit WIP LM5069
2024-02-28 Commit current WIP.
2024-03-06 Commit current WIP
2024-03-13 Commit initial complete placement.
2024-04-01 BOM updates WIP
2024-04-02 Update parts for availability
2024-04-03 Filled in more component parameters
2024-04-03 Swapping in parts for availability
2024-04-03 Added fuses and extra power connector.
2024-04-08 Commit current CAM
2024-04-08 Commit MFG zip file
2024-06-09 Commit B9 updates.
2024-06-09 Commit project files.
2025-11-12 Create LICENSE
2025-11-12 Added AutoDesk EAGLE Schematic
2025-11-12 Updated schematic
2025-11-12 Updated schematic (Incorrectly named NET)
2025-11-27 Fix disconnected nets on BAT54S components
